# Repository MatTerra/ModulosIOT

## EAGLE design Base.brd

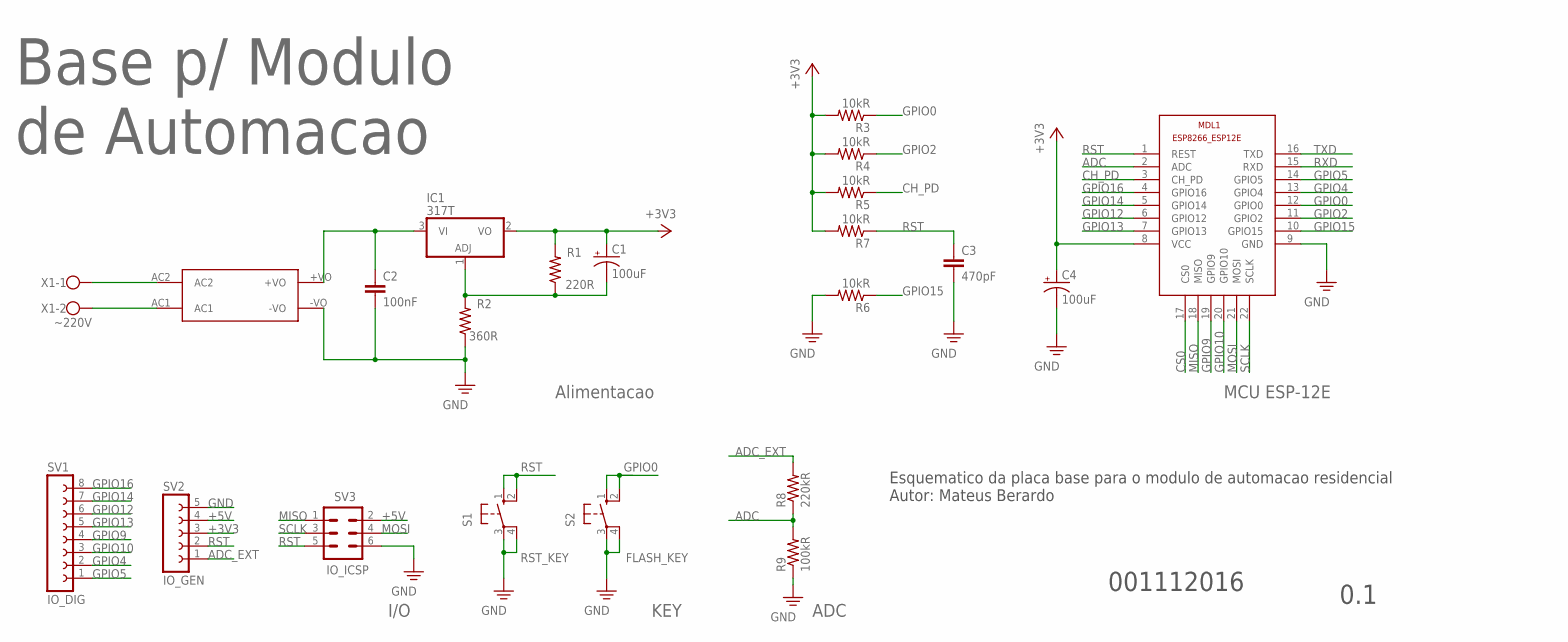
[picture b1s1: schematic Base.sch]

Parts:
C1, C4: 100uF; E3,5-8
C2: 100nF; C050-055X075
C3: 470pF; C050-055X075
IC1: 317T; TO220H
MDL1: MCU ESP; ESP8266-ESP12E
R1: 220R; 0207/10
R2: 360R; 0207/10
R3, R4, R5, R6, R7: 10kR; 0207/10
R8: 220kR; 0207/10
R9: 100kR; 0207/10
S1: RST_KEY; B3F-10XX
S2: FLASH_KEY; B3F-10XX
SV1: IO_DIG; FE08
SV2: IO_GEN; FE05-1
SV3: IO_ICSP; MA03-2
U$1: HLK-PM01
X1: ~220V; W237-102

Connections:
+3V3: C1.+, C4.+, IC1.2 (VO), MDL1.8 (VCC), R1.2, R3.2, R4.2, R5.2, R7.2, SV2.3
+5V: C2.1, IC1.3 (VI), SV2.4, SV3.2, U$1.+VO
+220: U$1.AC2, X1.1
-220V: U$1.AC1, X1.2
ADC: MDL1.2 (ADC), R8.1, R9.2
ADC_EXT: R8.2, SV2.1
ADJ: C1.-, IC1.1 (ADJ), R1.1, R2.2
CH_PD: MDL1.3 (CH_PD), R5.1
CS0: MDL1.17 (CS0)
GND: C2.2, C3.2, C4.-, MDL1.9 (GND), R2.1, R6.2, R9.1, S1.3, S1.4 (P1), S2.3, S2.4 (P1), SV2.5, SV3.6, U$1.-VO
GPIO0: MDL1.12 (GPIO0), R3.1, S2.1 (S), S2.2 (S1)
GPIO2: MDL1.11 (GPIO2), R4.1
GPIO4: MDL1.13 (GPIO4), SV1.2
GPIO5: MDL1.14 (GPIO5), SV1.1
GPIO9: MDL1.19 (GPIO9), SV1.4
GPIO10: MDL1.20 (GPIO10), SV1.3
GPIO12: MDL1.6 (GPIO12), SV1.6
GPIO13: MDL1.7 (GPIO13), SV1.5
GPIO14: MDL1.5 (GPIO14), SV1.7
GPIO15: MDL1.10 (GPIO15), R6.1
GPIO16: MDL1.4 (GPIO16), SV1.8
MISO: MDL1.18 (MISO), SV3.1
MOSI: MDL1.21 (MOSI), SV3.4
RST: C3.1, MDL1.1 (REST), R7.1, S1.1 (S), S1.2 (S1), SV2.2, SV3.5
RXD: MDL1.15 (RXD)
SCLK: MDL1.22 (SCLK), SV3.3
TXD: MDL1.16 (TXD)

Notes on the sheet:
Alimentacao
MCU ESP-12E
Base p/ Modulo de Automacao
001112016
Esquematico da placa base para o modulo de automacao residencial Autor: Mateus Berardo
0.1
I/O
KEY
ADC

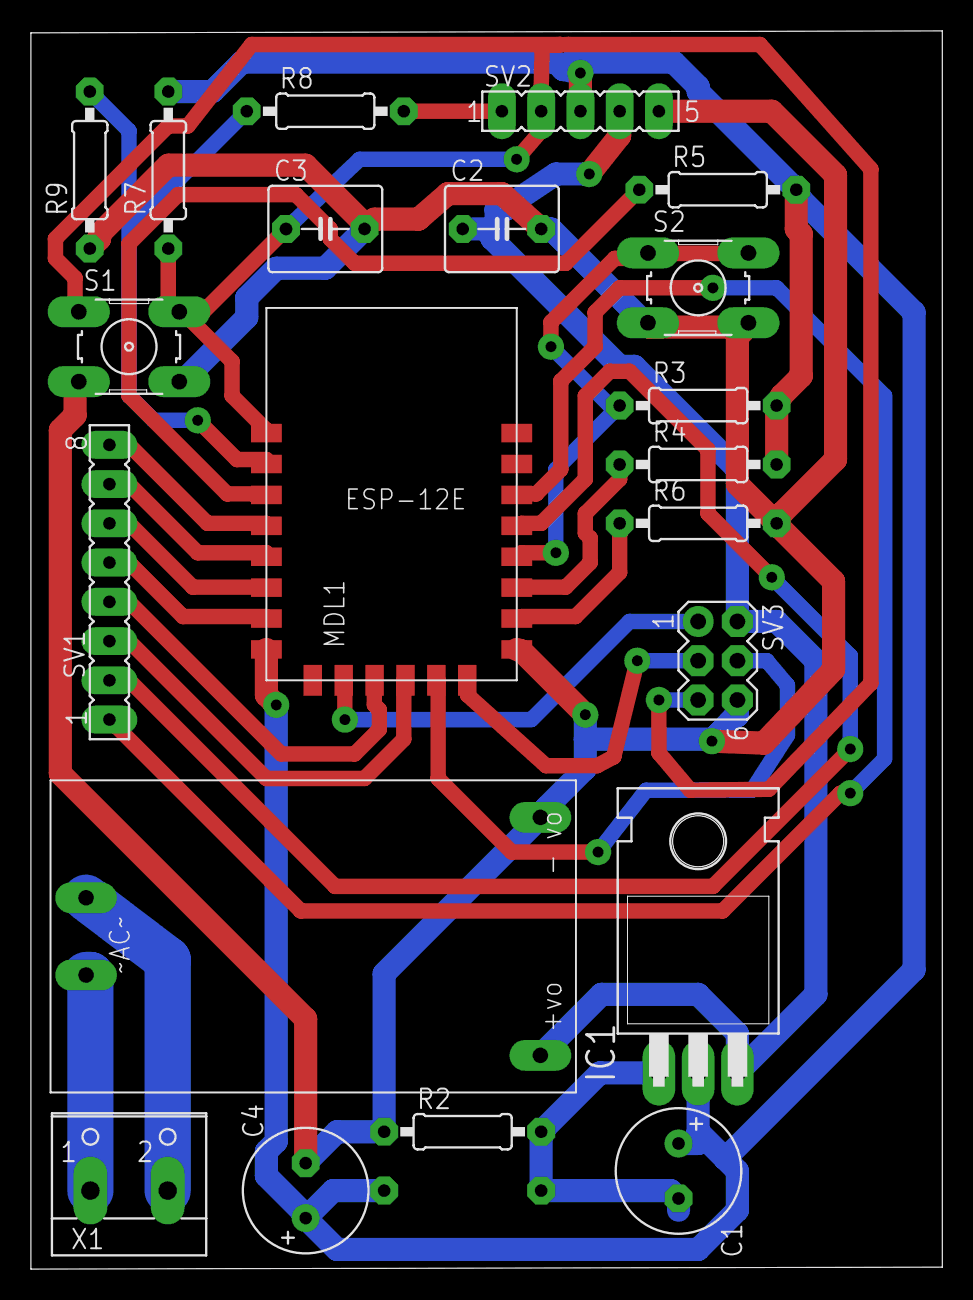
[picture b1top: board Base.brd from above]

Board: 2 copper layers, 59.0 x 80.1 mm, 22 parts (1 on the bottom side), 24 nets.

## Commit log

2016-12-13 first commit \n added first designs
2016-12-13 Readme
2016-12-13 add .gitignore
